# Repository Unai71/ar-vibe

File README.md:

# Hifimist 

## Vintage 70's cassette from ar-systems restomod

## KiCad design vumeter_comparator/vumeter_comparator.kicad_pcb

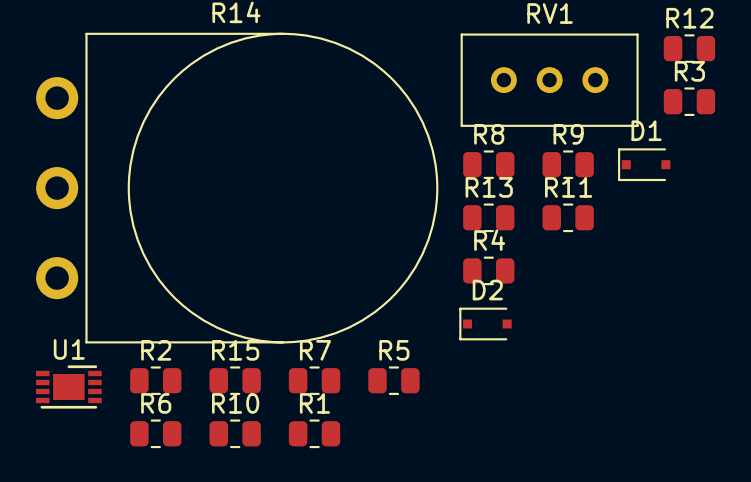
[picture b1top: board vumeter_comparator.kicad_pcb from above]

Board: 2 copper layers, 19 parts (0 on the bottom side), 12 nets, no tracks yet.

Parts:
D1, D2: PMEG4010CEJ; D_SOD-323F
R1, R2, R10, R11, R12, R13: 3.3k; R_0805_2012Metric
R3: 100; R_0805_2012Metric
R4, R5, R7, R8, R9: 47k; R_0805_2012Metric
R6, R15: R; R_0805_2012Metric
R14: 10k; Potentiometer_Omeg_PC16BU_Vertical
RV1: 5k; Potentiometer_Bourns_3296W_Vertical
U1: MCP6002-xMC; DFN-8-1EP_3x2mm_P0.5mm_EP1.75x1.45mm

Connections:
/Vumeter_gnd: D2.2 (A), R6.1
/Vumeter_positive: D1.1 (K), R15.1
GND: R6.2, R7.1, R8.2, R9.2, R13.1, R15.2
unnamed: R2.2, U1.1
unnamed: R11.1, R12.1, R13.2
unnamed: R1.1, R5.2, U1.2 (-)
unnamed: R1.2, R2.1, RV1.2, RV1.3
unnamed: R3.2, R14.2
unnamed: R4.2, R10.2, U1.3 (+)
unnamed: D1.2 (A), D2.1 (K), R7.2
unnamed: R3.1, R10.1, R11.2
unnamed: R14.1, RV1.1

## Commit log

2021-08-30 Added schematics for the vumeter comparator circuit v0.1
